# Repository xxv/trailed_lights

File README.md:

Trailed Lights
==============

Wifi-connected jar lanterns.

This is an experiment / art project playing around with expectations. What do
you expect of a simple Ball jar lantern lining a trail in the woods at a burn?
It's likely just some cheap string lights and batteries. It may dim over time
as the batteries run out. The lights may not work at all, but hopefully someone
changed the batteries.

But what if they could interact with you?

These are Ball jar-based lanterns that are expected to last about 5 days on a
charge. They have ambient light sensors and motion detectors to help save power
and to allow interactions with people.

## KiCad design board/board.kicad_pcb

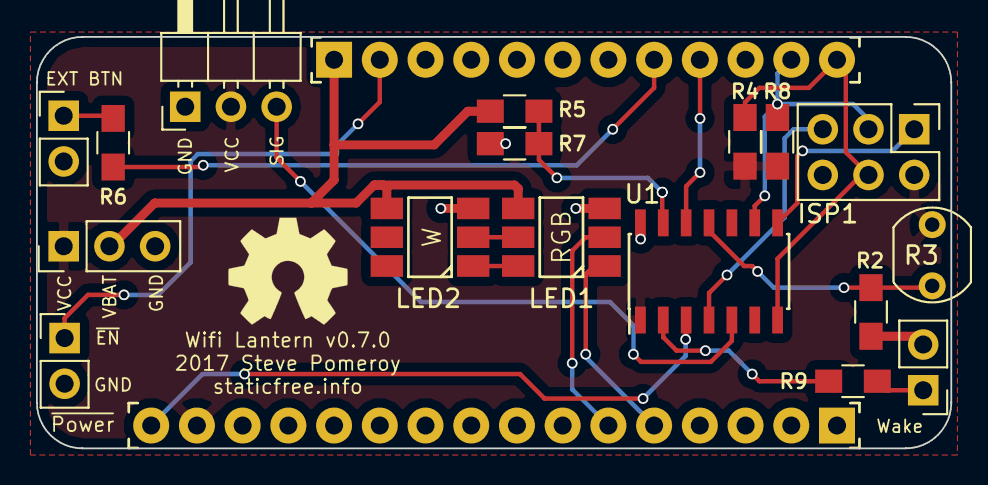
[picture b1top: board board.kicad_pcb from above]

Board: 2 copper layers, 50.8 x 22.9 mm, 19 parts (0 on the bottom side), 21 nets.

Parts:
ISP1: AVR-ISP-6; Pin_Header_Straight_2x03_Pitch2.54mm
J1: MOTION DETECTOR; Pin_Header_Angled_1x03_Pitch2.54mm
J2: EXT BUTTON; Pin_Header_Straight_1x02_Pitch2.54mm
J3: EXT WAKE; Pin_Header_Straight_1x02_Pitch2.54mm
J4: ~POWER; Pin_Header_Straight_1x02_Pitch2.54mm
J5: GPWR; Pin_Header_Straight_1x03_Pitch2.54mm
JP1: PinHeader_01x16_2.54mm; Conn_PinHeader_1x16
JP3: PinHeader_01x12_2.54mm; Conn_PinHeader_1x12
LED1: APA102 (RGB); APA102_hand_solder
LED2: APA102 (W); APA102_hand_solder
R2: 10K; R_0805_HandSoldering
R3: R_PHOTO; Resistor_LDR_5.1x4.3_RM3.4
R4, R8: 4.7K; R_0805_HandSoldering
R5: 12K; R_0805_HandSoldering
R6, R9: 1K; R_0805_HandSoldering
R7: 30K; R_0805_HandSoldering
U1: ATTINY841-SSU; SOIC-14_3.9x8.7mm_Pitch1.27mm

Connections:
/AMBIENT: R2.1, R3.2, U1.11
/ATY_MISO: ISP1.1, U1.8
/ATY_MOSI: ISP1.4, JP3.12, R4.2, U1.7
/ATY_SCK: ISP1.3, JP3.11, R8.2, U1.9
/BAT_MON: R5.2, R7.1, U1.13
/D6: JP3.9, U1.12
/D9: JP3.8, R6.2
/EN: J4.1, JP3.2
/EXT_WAKE: R9.2, U1.2
/MOSI: JP1.5, LED1.1
/MOTION_SIG: J1.3, U1.5
/SCK: JP1.6, LED1.2
/VBAT: J5.2, JP3.1, LED1.4, LED2.4, R5.1
/~ATY_RST: ISP1.5, U1.4
/~RESET: JP1.16, U1.3
GND: ISP1.6, J1.1, J2.2, J3.2, J4.2, J5.3, JP1.13, LED1.3, LED2.3, R2.2, R7.2, U1.14
unnamed: J2.1, R6.1
unnamed: J3.1, R9.1
unnamed: LED1.5, LED2.2
unnamed: LED1.6, LED2.1
VCC: ISP1.2, J1.2, J5.1, JP1.15, R3.1, R4.1, R8.1, U1.1

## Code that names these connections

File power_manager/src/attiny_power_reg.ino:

#include <avr/sleep.h>
#include <WireS.h>

// Pin mapping (Arduino pin numbers)
const static byte BAT_MON_PIN   = A0;
const static byte AMBIENT_PIN   = A2;
const static byte ESP_RESET_PIN = PIN_B1;
const static byte ESP_RTC_PIN   = PIN_A1;
const static byte EXT_WAKE_PIN  = PIN_B0;
const static byte MOTION_PIN    = PIN_B2;

const static byte MY_I2C_ADDR = 0x50;
const static byte REG_BATTERY_LEVEL = 0x01;
const static byte REG_AMBIENT_LEVEL = 0x02;
const static byte REG_TEST = 0x03;

// timings
const static byte RESET_TIME    = 100;

const static byte CMD_GET_BATT   = 0x62;
const static byte CMD_SET_RTC_EN = 0x72;
const static byte CMD_SLEEP_NOW  = 0x7A;

// Calibrations
const static int BATTERY_VAL_LOW  = 718;
const static int BATTERY_VAL_HIGH = 956;
const static int AMBIENT_VAL_ON   = 200; // 1.0v
const static int AMBIENT_VAL_OFF  = 100; // 1.0v

static bool wake_on_rtc = true;
static bool wake_on_motion = true;
static bool wake_on_external = true;

bool is_dark = true;
uint8_t last_motion = 0xff;
uint8_t last_ext_wake = 0xff;
uint8_t last_esp_reset = 0xff;
uint8_t current_register = 0;

uint8_t test_value = 0;

volatile uint8_t trigger_source = 0;
volatile bool triggered = false;
volatile unsigned long triggered_time = 0;

ISR(PCINT0_vect) {
  triggered = true;
  triggered_time = millis();
}

ISR(PCINT1_vect) {
  triggered = true;
  triggered_time = millis();
}

/**
 * Enable Pin Change Interrupt on given pin number.
 */
void pciSetup(byte pin) {
  bitSet(*digitalPinToPCMSK(pin), digitalPinToPCMSKbit(pin)); // enable pin
  bitSet(*digitalPinToPCICR(pin), digitalPinToPCICRbit(pin)); // enable interrupt
}

/**
 * Enable sleep mode and turn on pin change interrupt
 */
void sleepNow() {
  set_sleep_mode(SLEEP_MODE_PWR_DOWN);
  sleep_enable();

  // -.- zzz...
  sleep_mode();

  // !! O.O
  sleep_disable();

  disable_interrupts();
}

void enable_interrupts() {
  // Enable PC interrupt
  if (wake_on_motion) {
    pciSetup(MOTION_PIN);
  }

  if (wake_on_external) {
    pciSetup(EXT_WAKE_PIN);
    pinMode(EXT_WAKE_PIN, INPUT_PULLUP);
  }

  if (wake_on_rtc) {
    pciSetup(ESP_RTC_PIN);
  }
}

void disable_interrupts() {
  // Disable PC interrupt
  if (wake_on_motion) {
    bitClear(*digitalPinToPCICR(MOTION_PIN),
              digitalPinToPCICRbit(MOTION_PIN));
  }

  if (wake_on_external) {
    bitClear(*digitalPinToPCICR(EXT_WAKE_PIN),
              digitalPinToPCICRbit(EXT_WAKE_PIN));
  }

  if (wake_on_rtc) {
    bitClear(*digitalPinToPCICR(ESP_RTC_PIN),
              digitalPinToPCICRbit(ESP_RTC_PIN));
  }
}

int getAmbient() {
  return analogRead(AMBIENT_PIN);
}

uint8_t getAmbientByte() {
  return map(analogRead(AMBIENT_PIN), 0, 1023, 0, 255);
}

uint8_t getBattery() {
  return constrain(map(analogRead(BAT_MON_PIN),
                       BATTERY_VAL_LOW, BATTERY_VAL_HIGH, 0, 100),
                   0, 100);
}

void onReceive(size_t num_bytes) {
  if (num_bytes == 0) {
    return;
  }

  current_register = Wire.read();
  num_bytes--;

  while (Wire.available()) {
    Wire.read();
  }
}

void onRequest() {
  if (current_register == REG_BATTERY_LEVEL) {
    Wire.write(getBattery());
  } else if (current_register == REG_AMBIENT_LEVEL) {
    Wire.write(getAmbientByte());
  } else if (current_register == REG_TEST) {
    Wire.write(test_value++);
  }

  current_register = 0;
}

void wake_esp() {
  digitalWrite(ESP_RESET_PIN, LOW);
  delay(RESET_TIME);
  digitalWrite(ESP_RESET_PIN, HIGH);
  delay(RESET_TIME);
}

void setup() {
  pinMode(ESP_RESET_PIN, OUTPUT);
  pinMode(AMBIENT_PIN, INPUT);
  pinMode(BAT_MON_PIN, INPUT);

  pinMode(MOTION_PIN, INPUT);
  pinMode(EXT_WAKE_PIN, INPUT);
  pinMode(ESP_RTC_PIN, INPUT);

  Wire.begin(MY_I2C_ADDR);
  Wire.onReceive(onReceive);
  Wire.onRequest(onRequest);

  // Reset output is active low
  digitalWrite(ESP_RESET_PIN, HIGH);

  enable_interrupts();
}

void loop() {
  if (triggered && (millis() - triggered_time) > 50) {
    // only handle trigger on risen edge
    uint8_t motion_val = !digitalRead(MOTION_PIN);
    uint8_t ext_wake_val = digitalRead(EXT_WAKE_PIN);
    uint8_t esp_reset_val = digitalRead(ESP_RESET_PIN);
    if (is_dark &&
        ((motion_val != last_motion && last_motion)
          || (ext_wake_val  != last_ext_wake  && ext_wake_val)
          || (esp_reset_val != last_esp_reset && esp_reset_val))) {
        wake_esp();
    }

    triggered = false;
    enable_interrupts();
    last_ext_wake = ext_wake_val;
    last_esp_reset = esp_reset_val;
    last_motion = motion_val;
  }

  int ambient = getAmbient();

  if (!is_dark && ambient >= AMBIENT_VAL_ON) {
    is_dark = true;
  } else if (is_dark && ambient <= AMBIENT_VAL_OFF) {
    is_dark = false;
  }
  delay(10);
}

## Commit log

2017-03-17 Improve animation; follows mouse
2017-03-24 Render using canvas gradients
2017-03-25 Simplify
2017-03-26 Add first draft of art grant proposal
2017-03-26 Apply Care's edits
2017-03-27 First working version of controller + lantern sim
2017-03-27 Change signal hierarchy
2017-03-28 Add support for python2
2017-03-28 Add remote control
2017-03-28 Add trip status info
2017-03-28 Add controller status info
2017-03-29 Improve remote control
2017-03-29 Add remote
2017-03-31 Add animation class to do simple linear animations
2017-04-03 First pass at lantern ESP8266 device
2017-04-03 Use hex colors; add connected status
2017-04-03 Remove debug messages
2017-04-04 Turn off LED on pin 0
2017-04-06 Set motion pin to one not already in use; keep color after reboot
2017-04-12 Remove SSL connection from lantern
2017-04-12 Lantern: don't reset to black on boot
2017-04-12 Update lantern sim and controller with pylint
2017-04-12 Add mqtt_base
2017-04-12 Fix controller and lantern
2017-04-13 Add MQTT integration to js demo
2017-04-14 Add trip counter and reset
2017-04-14 Sim: Add support for color
2017-04-14 Fix brightness
2017-04-21 Small browser tweaks
2017-04-22 Fix controller bug which prevented trips from starting
2017-04-22 Move config file loading to base lib
2017-04-22 Fix javascript client ID
2017-04-22 Show remote triggering of motion
2017-04-22 Add localhost.html
2017-04-22 Fix remote crash on blank line
2017-04-22 Fix retriggering
2017-05-04 Fix motion on same trip
2017-05-04 Fix default brightness
2017-05-04 Advance all trips on motion
2017-05-05 Add support for trip intersections
2017-06-22 Add housing
2017-06-23 Add motion detector mounting bracket
2017-07-30 Add sleep command
2017-07-30 Add first pass at board
2017-08-03 Add attiny85 to control power
2017-08-06 Add protection resistors
2017-08-07 Rework
2017-08-07 Move ISP header further from LEDs to prevent shadows
2017-08-08 Move headers so they'll fit inside a jar
2017-08-08 Move motion detector header further inward
2017-08-09 Fix photoresistor circuit
2017-08-09 Move photoresistor in housing
2017-08-12 Add I2C lines between between attiny and ESP8266
2017-08-13 Revision
2017-08-13 Add power button and GPIO16 reset jumper
    * Remove redundant resistors
2017-08-13 Clean up fab layer
2017-08-13 Add feather mounting brackets
2017-08-13 Housing: add Feather bracket; room for battery
2017-08-13 Tweak part hole placement
2017-08-18 Board updates
2017-08-18 Add Attinyx5-based power manager
2017-08-20 Add power breakout; updated on-board docs
2017-08-20 Improve on-board docs
2017-08-20 Remove 3D model for extra power breakout
2017-08-21 Update board to add power breakout
2017-08-22 Rework board to use Attiny84
    MOAR GPIOS!
    * Add battery level monitor
    * Move RTC signal to power controller
    * Add external wake signal breakout
2017-08-22 attiny_power_reg ws change
2017-08-22 Port pin change interrupts to arduino
2017-08-22 Add new pins for attiny84
2017-08-26 Switch footprint part number
2017-09-07 Fix up power manager interrupts
    * add pull-up
    * add 50ms debounce timeout
2017-09-08 Cleanup
2017-09-08 Use device ID for MQTT client ID
2017-10-07 Final pass at preserving LED state across deep sleeps
2017-10-07 Upgrade to kicad 4.0.7
2017-10-07 Add simple crossfade animation for color setting
    * Save LED state across deep sleeps
2017-10-07 Move to new Arduino framework; add ambient support
2017-10-07 Add GPIO header; move attiny further from LEDs
2017-10-07 Move motion tracking to power manager; add white LED
2017-10-07 Add power manager
2017-10-07 Add first pass at ESP8266 I2C control
2017-10-07 Add attiny tinywire client
2017-10-07 Uncomment commented code
2017-10-07 Board revision 2
    * Only connect motion detector to power manager
    * Move ambient sensor to power manager
    * Increase spacing on LEDs; move to hand solder footprint
2017-10-11 Default to the printed part in housing
2017-10-11 Fix broken ambient logic
2017-10-11 Volatile variables are volatile
2017-10-11 Motion value is inverted
2017-10-11 Add two new power manager registers: motion and sleep
2017-10-11 Add attiny test register
2017-10-11 Add default color
2017-10-11 Add battery power down
2017-10-11 Add gentle fade off
2017-10-11 Update power manager to use attiny841
2017-10-11 Default timeout to 15s; sub before pub
2017-10-11 Iterate housing measurements based on 3D print
2017-10-11 Publish JSON status reports
2017-10-11 Stretch that clock
2017-10-11 Calibrate battery
2017-10-11 Remove unused library
2017-10-11 Consolidate debug messages
2017-10-11 Fix bug with ESP talking to attiny
2017-10-11 Add critical battery protection
2017-10-11 Unify register reading
2017-10-11 Move ADC sampling to main loop
2017-10-11 Add RTC memory fingerprint to avoid weird colors on power up
2017-10-11 Remove stray decrement
2017-10-11 Add configurable motion timeout
2017-10-11 Move to proper "sensors" topic; cleanup
2017-10-11 Add global color/white and re-order subscription checks
2017-10-11 Publish status update automatically
2017-10-11 Add secrets-set SSL setting
2017-10-11 Debugging messages
2017-10-12 Add README
2017-10-12 Turn off light when it's bright out
